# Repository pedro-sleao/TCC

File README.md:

# Sistema Embarcado com comunicação WiFi para monitoramento de variáveis da água para Carcinicultura

Este projeto visa desenvolver um sistema embarcado com conectividade Wi-Fi para monitoramento remoto de variáveis da água, com foco em aplicações na carcinicultura. O sistema coleta dados de sensores, realiza a transmissão via protocolo MQTT e oferece suporte para atualizações OTA.

## Sensores

- **Sensor de temperatura DS18B20**
- **Sensor de PH Ph4502c**
- **Sensor de TDS**
- **Sensor de turbidez**

## Pinagem
 
| DS18B20 |  ESP32
| --------| ---------------
| VCC     |  GPIO16
| GND     |  GND
| 1-Wire bus |  GPIO4

| Ph4502c |  ESP32
| --------| ---------------
| VCC     |  Bateria 5V
| GND     |  Chave controlada pela ESP (GPIO18)
| P0      |  ADC1_CHANNEL_4 (Com divisor de tensão)

| TDS |  ESP32
| --------| ---------------
| VCC     |  GPIO17
| GND     |  GND
| P0      |  ADC1_CHANNEL_3

| Turbidez |  ESP32
| --------| ---------------
| VCC     |  GPIO19
| GND     |  GND
| P0      |  ADC1_CHANNEL_5

## Status do projeto

### Firmware

- [x] OTA
- [x] Sensores
- [x] SmartConfig (Conectar a esp ao WiFi utilizando o celular)
- [x] WiFi
- [x] MQTT
- [x] Usar o RTC para enviar os dados periodicamente

### PCB

- [x] Definir se os sensores serão alimentados diretamente pela ESP32 ou por uma fonte externa -> sensor de pH pelos 5V do módulo da bateria e os outros sensores pela esp
- [x] Decidir o que será utilizado para adaptar a saída do sensor de PH (0 - 5V) para a entrada do ADC da ESP (0 - 3.3V) -> divisor de tensão
- [x] Finalizar o esquemático com todos os componentes
- [x] Layout da Placa

### Back-end

- [x] Receber os dados por MQTT
- [x] Inserir os dados no banco de dados
- [x] API para enviar os dados para o frontend
- [x] Websocket para notificar a chegada de novos dados

### Front-end

- [x] Obter os dados da API
- [x] Página principal do dashboard
- [x] Página de registro das placas
- [x] Página de cadastro de usuários
- [ ] Página de calibração dos sensores

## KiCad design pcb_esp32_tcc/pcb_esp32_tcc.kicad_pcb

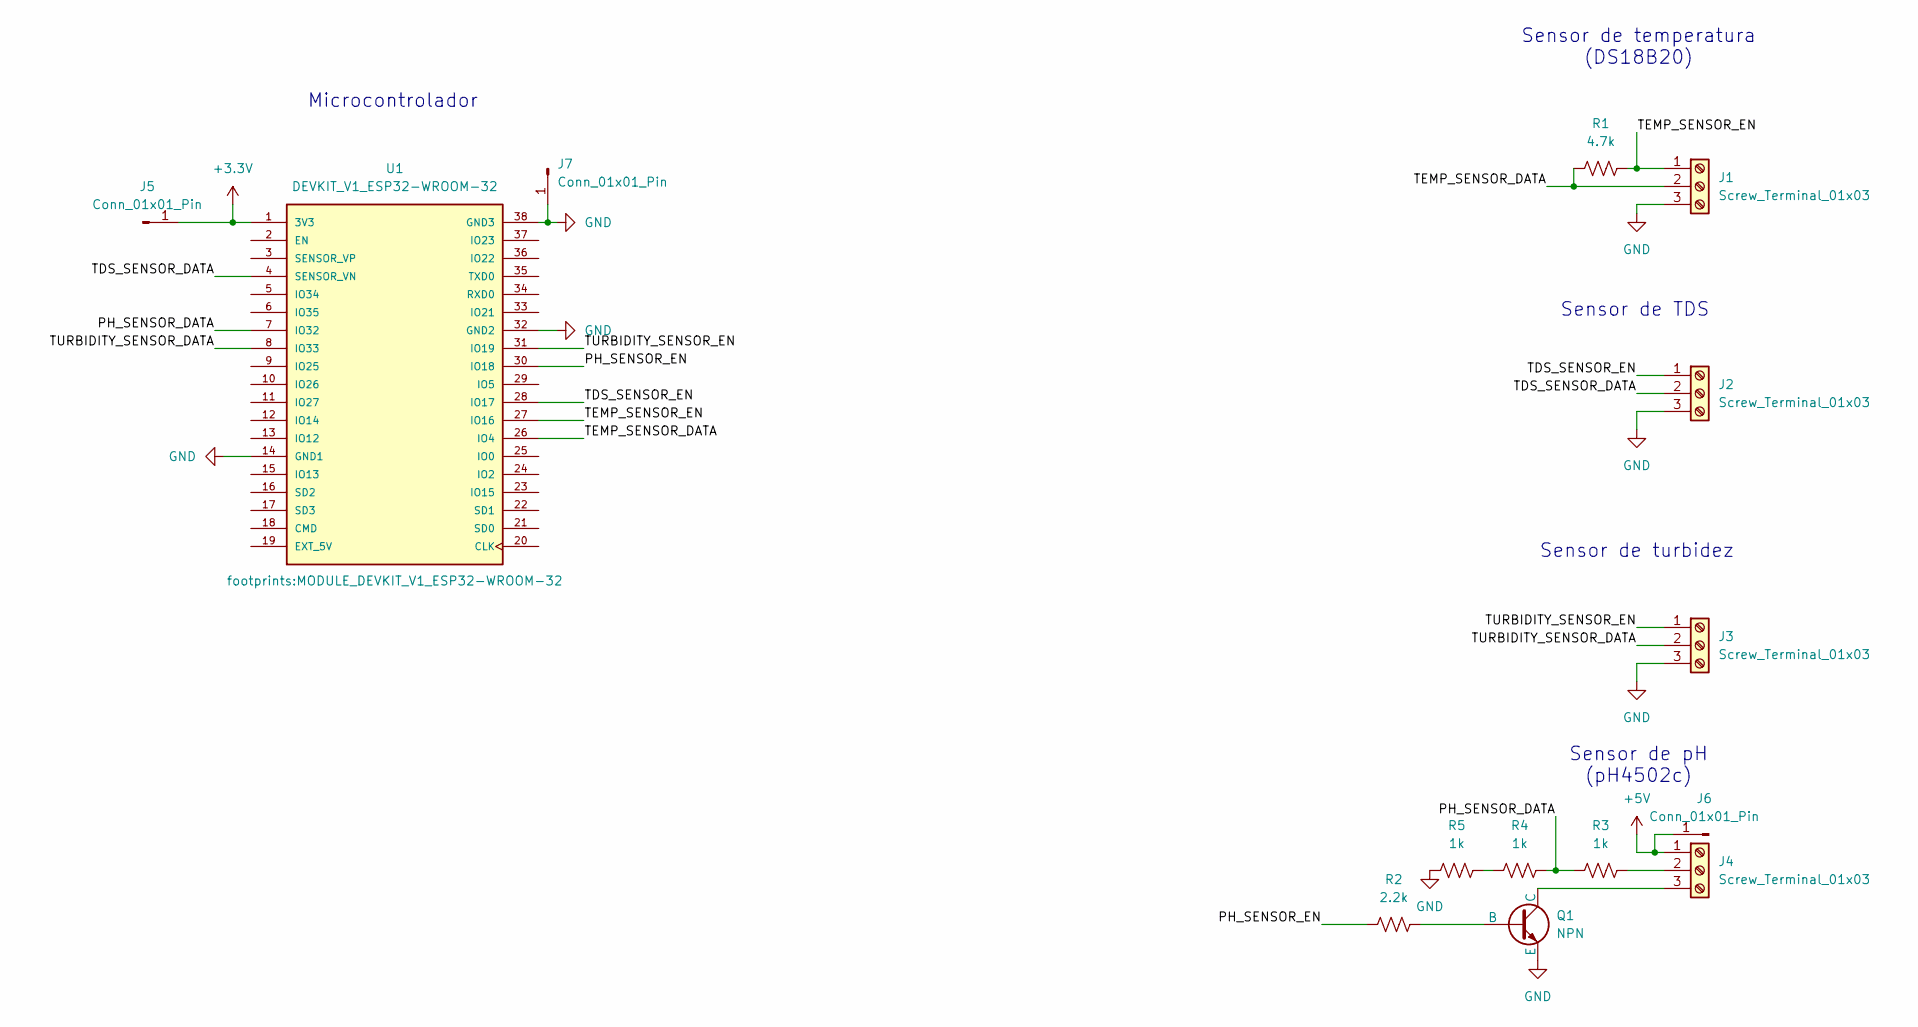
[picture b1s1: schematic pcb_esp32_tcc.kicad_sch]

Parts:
J1, J2, J3, J4: Screw_Terminal_01x03; TerminalBlock_Phoenix_MKDS-1,5-3-5.08_1x03_P5.08mm_Horizont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
J5, J6, J7: Conn_01x01_Pin; PinHeader_1x01_P2.54mm_Vertical
Q1: NPN; TO-92_Inline_Wide
R1: 4.7k; R_Axial_DIN0309_L9.0mm_D3.2mm_P12.70mm_Horizontal
R2: 2.2k; R_Axial_DIN0309_L9.0mm_D3.2mm_P12.70mm_Horizontal
R3, R4, R5: 1k; R_Axial_DIN0309_L9.0mm_D3.2mm_P12.70mm_Horizontal
U1: DEVKIT_V1_ESP32-WROOM-32; MODULE_DEVKIT_V1_ESP32-WROOM-32; PARTREV N/A

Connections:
+3.3V: J5.1, U1.1 (3V3)
+5V: J4.1, J6.1
/PH_SENSOR_DATA: R3.1, R4.2, U1.7 (IO32)
/PH_SENSOR_EN: R2.1, U1.30 (IO18)
/TDS_SENSOR_DATA: J2.2, U1.4 (SENSOR_VN)
/TDS_SENSOR_EN: J2.1, U1.28 (IO17)
/TEMP_SENSOR_DATA: J1.2, R1.1, U1.26 (IO4)
/TEMP_SENSOR_EN: J1.1, R1.2, U1.27 (IO16)
/TURBIDITY_SENSOR_DATA: J3.2, U1.8 (IO33)
/TURBIDITY_SENSOR_EN: J3.1, U1.31 (IO19)
GND: J1.3, J2.3, J3.3, J7.1, Q1.3 (E), R5.1, U1.14 (GND1), U1.32 (GND2), U1.38 (GND3)
unnamed: J4.2, R3.2
unnamed: J4.3, Q1.1 (C)
unnamed: Q1.2 (B), R2.2
unnamed: R4.1, R5.2

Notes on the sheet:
Microcontrolador
Sensor de pH (pH4502c)
Sensor de temperatura (DS18B20)
Sensor de turbidez
Sensor de TDS

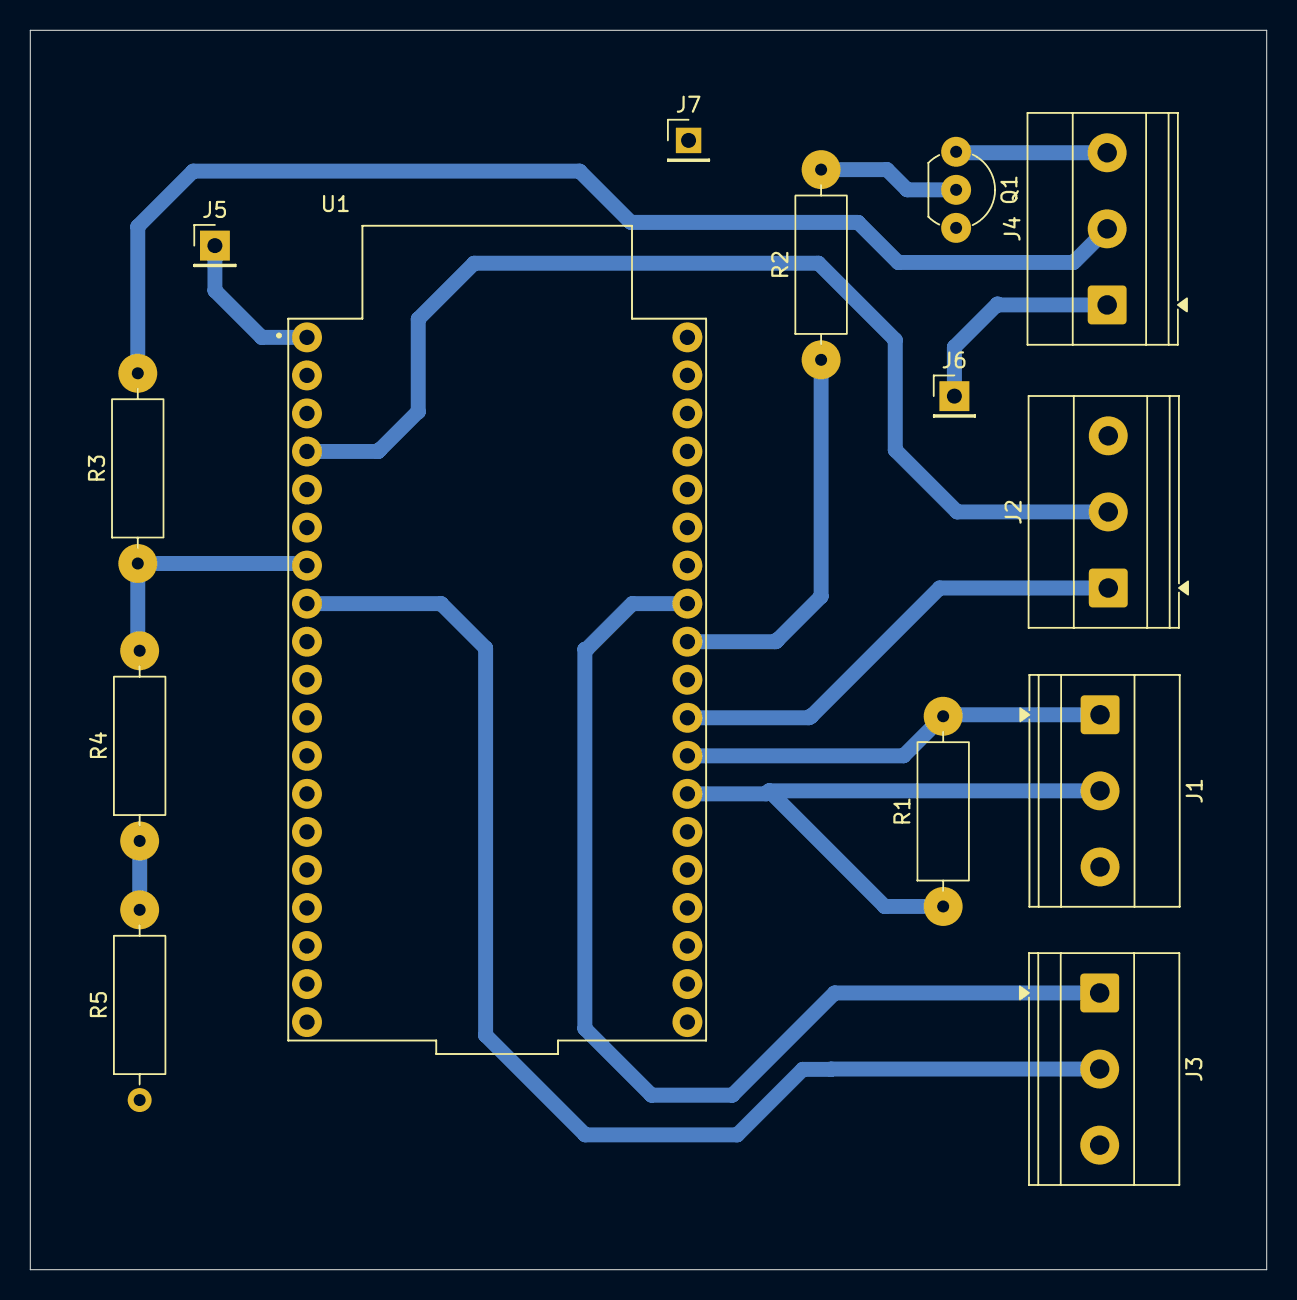
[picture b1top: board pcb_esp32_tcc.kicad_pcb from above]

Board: 2 copper layers, 82.6 x 82.8 mm, 14 parts (0 on the bottom side), 15 nets.

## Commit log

2025-01-27 Adding the files related to SmartConfig for ESP32. The tests were made for ESPTOUCH and ESPTOUCH_V2.
2025-01-27 Adding the files related to firmware update OTA and to the MQTT protocol. Tests were made using mosquitto broker and local Python server. Both features are working properly.
2025-01-28 Adding auto-connect feature for previously connected Wi-Fi on restart and refactor code into components for better modularization.
2025-02-04 Adding the power management configuration to enable auto light sleep.
2025-02-05 Adding adc manager component files. Tested with an LDR sensor. FreeRTOS task for ADC management needs to be implemented.
2025-02-10 Adding the sensors manager task and enable/disable sensor functions. Split component files into sensors_manager and adc_manager. Need to implement a file with the OneWire protocol to support the temp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
2025-02-11 Adding the files related to the ds18x20 sensor and the one wire protocol.
2025-02-12 Adding the publish function to the mqtt_service and testing it with the sensors_manager.
2025-05-05 Update README with project status
2025-05-06 Adding the RTC get the real time. Only made the RTC test need to change the code to use the RTC to send the data periodically.
2025-05-07 Adding the RTC to send the data periodically and fixing the smartconfig eventbits error.
2025-05-14 Adding the device id to the mqtt message. Used the esp esfuse to get the mac address of the device to use as an id for the board
2025-07-04 Pequenas correções nos sensores e no OTA
2025-07-05 Addign the ADC calibration and the TDS measurement
2025-07-05 Converting the TDS voltage to ppm
2025-07-07 Changing the mqtt topic standard
2025-07-07 Adding the pH sensor
2025-07-09 Implementing the pcb schematic and design
2025-07-09 Update esp32 footprint and symbol
2025-07-12 Adding the LWT message to MQTT and split the time sync functions to another component
2025-07-12 Adding the MQTT_SEND_DATA_EVENT to send sensors data when asked
2025-07-12 Starting to implement the server. Created the mqtt client on server side.
2025-07-13 Modifying the endpoints data processing. MQTT data receiving is ok.
2025-07-14 Adding the frontend made in Flutter
2025-07-22 Fixing some erros and adding the firmware version to the device status
2025-07-22 Adding the OTA page to the flutter app and ota endpoints on the server
2025-07-22 Implementing the sensors calibration task
2025-07-23 Implementing the tds calibration task
2025-07-24 Implementing the sensors calibration endpoint
2025-07-24 Sensor calibration working and implementation of the request data button
2025-07-25 Mobile version working
2026-04-16 versao final
